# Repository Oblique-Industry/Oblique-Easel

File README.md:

# Oblique Easel
 Code, Electronics, and Industrial Design for the Oblique Easel Artmaschine Cyberdeck

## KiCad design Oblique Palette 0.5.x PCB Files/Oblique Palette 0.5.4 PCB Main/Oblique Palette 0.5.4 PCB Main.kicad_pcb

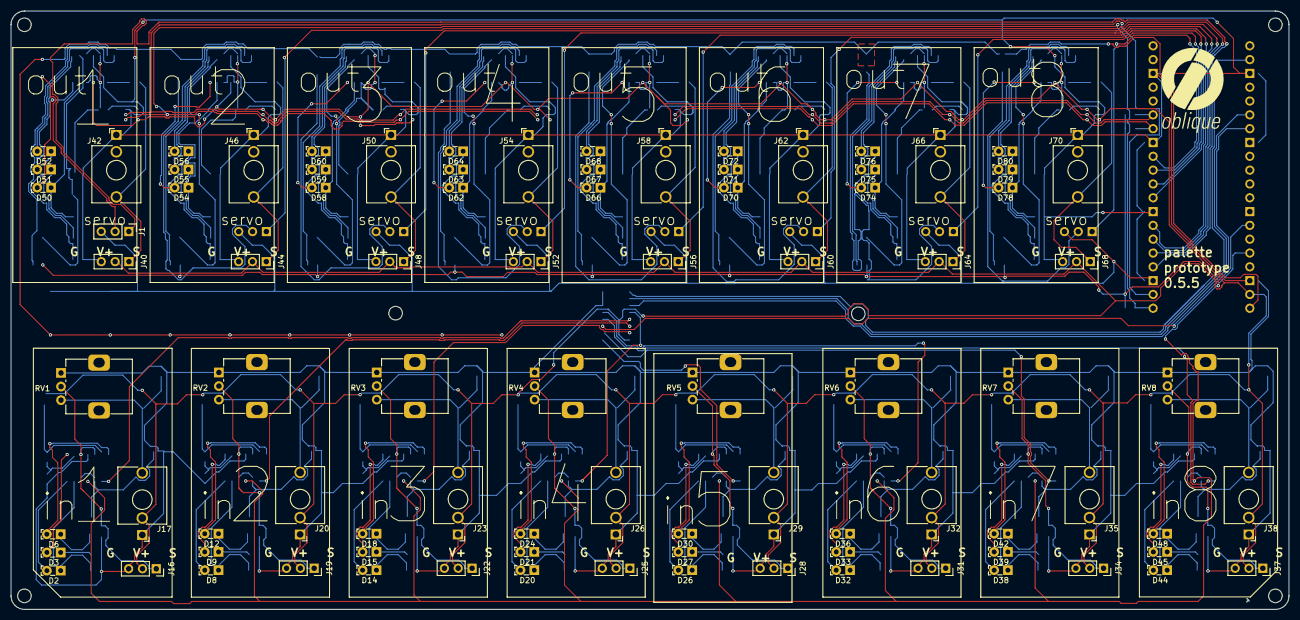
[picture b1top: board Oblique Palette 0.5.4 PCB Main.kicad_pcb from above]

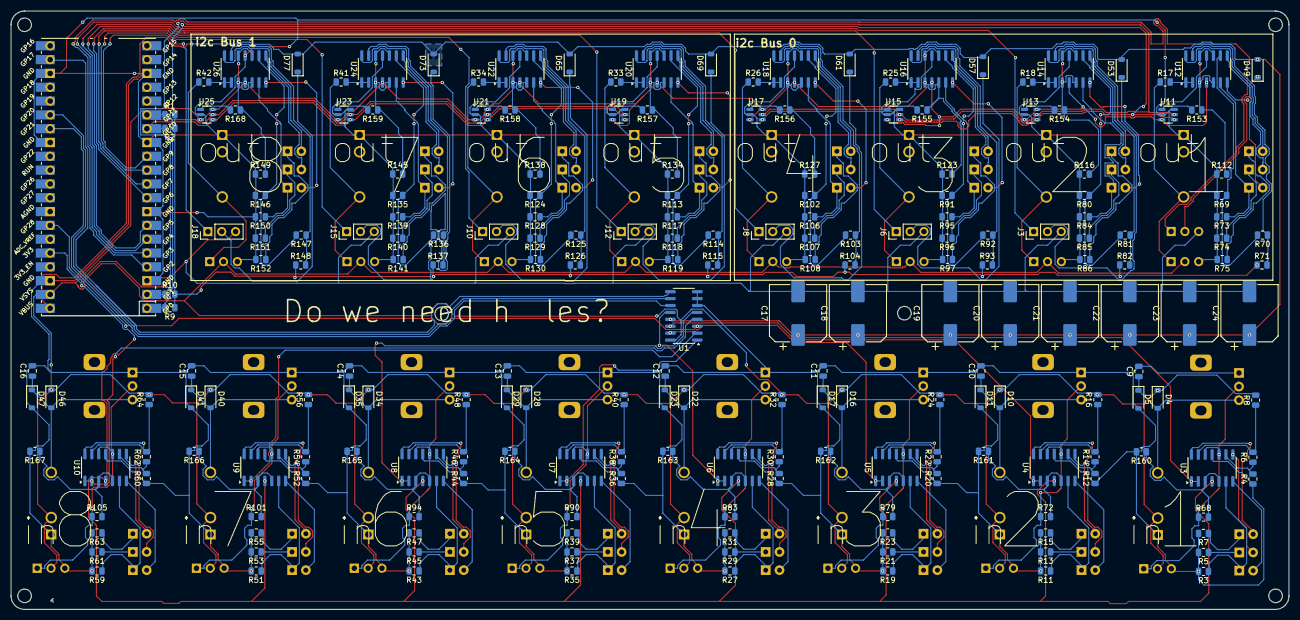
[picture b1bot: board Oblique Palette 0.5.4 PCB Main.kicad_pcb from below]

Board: 2 copper layers, 235.0 x 110.0 mm, 304 parts (213 on the bottom side), 220 nets.

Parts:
C9, C10, C11, C12, C13, C14, C15, C16: 1n; C_0805_2012Metric
C17, C18, C19, C20, C21, C22, C23, C24: 1mF; CP_Elec_10x10
D2, D8, D14, D20, D26, D32, D38, D44, D50, D54, D58, D62, D66, D70, D74, D78: White; LED_SideEmitter_Rectangular_W4.5mm_H1.6mm
D3, D9, D15, D21, D27, D33, D39, D45, D51, D55, D59, D63, D67, D71, D75, D79: Yellow; LED_SideEmitter_Rectangular_W4.5mm_H1.6mm
D4, D5, D10, D11, D16, D17, D22, D23, D28, D29, D34, D35, D40, D41, D46, D47: 1N4148; D_SOD-123
D6, D12, D18, D24, D30, D36, D42, D48, D52, D56, D60, D64, D68, D72, D76, D80: Red; LED_SideEmitter_Rectangular_W4.5mm_H1.6mm
D49, D53, D57, D61, D65, D69, D73, D77: D_SOD-123
G1: LOGO; PCB silkscreen logo
G2: LOGO; PCB silkscreen logotype
J1, J3, J6, J8, J10, J12, J15, J18: Conn_01x03_Male_Pin; PinHeader_1x03_P2.54mm_Vertical
J16, J19, J22, J25, J28, J31, J34, J37, J40, J44, J48, J52, J56, J60, J64, J68: Conn_01x03_Female_Pin; PinSocket_1x03_P2.54mm_Vertical
J17, J20, J23, J26, J29, J32, J35, J38, J42, J46, J50, J54, J58, J62, J66, J70: AudioJack2_SwitchT; Jack_3.5mm_QingPu_WQP-PJ398SM_Vertical_CircularHoles
R1, R2, R9, R10: R33k; R_0805_2012Metric
R3, R11, R19, R27, R35, R43, R51, R59, R73, R84, R95, R106, R117, R128, R139, R150: 1K; R_0805_2012Metric
R4, R12, R20, R28, R36, R44, R52, R60, R69, R80, R91, R102, R113, R124, R135, R146: 300k; R_0805_2012Metric
R5, R7, R13, R15, R21, R23, R29, R31, R37, R39, R45, R47, R53, R55, R61, R63, R74, R75, R85, R86, R96, R97, R107, R108, R118, R119, R129, R130, R140, R141, R151, R152: 127R; R_0805_2012Metric
R6, R14, R22, R30, R38, R46, R54, R62: 110K; R_0805_2012Metric
R8, R16, R24, R32, R40, R48, R56, R64: 150K; R_0805_2012Metric
R17, R18, R25, R26, R33, R34, R41, R42: 100R; R_0805_2012Metric
R68, R72, R79, R83, R90, R94, R101, R105: 100K; R_0805_2012Metric
R70, R81, R92, R103, R114, R125, R136, R147: 110k; R_0805_2012Metric
R71, R82, R93, R104, R115, R126, R137, R148: 150k; R_0805_2012Metric
R112, R116, R123, R127, R134, R138, R145, R149: 200k; R_0805_2012Metric
R153, R154, R155, R156, R157, R158, R159, R168: 100k; R_0805_2012Metric
R160, R161, R162, R163, R164, R165, R166, R167: 200K; R_0805_2012Metric
RV1, RV2, RV3, RV4, RV5, RV6, RV7, RV8: R_Potentiometer_MountingPin; Potentiometer_Alps_RK09K_Single_Vertical
U1: CD4051B; SOIC-16_3.9x9.9mm_P1.27mm
U2: Pico; RPi_Pico_SMD_TH
U3, U4, U5, U6, U7, U8, U9, U10, U12, U14, U16, U18, U20, U22, U24, U26: MCP6004; SOIC-14_3.9x8.7mm_P1.27mm
U11, U13, U15, U17, U19, U21, U23, U25: MCP4725xxx-xCH; SOT-23-6

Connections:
+3.3V: R1.2, R2.1, R9.1, R10.2, R71.1, R82.1, R93.1, R104.1, R115.1, R126.1, R137.1, R148.1, U2.36 (3V3), U3.4 (V+), U4.4 (V+), U5.4 (V+), U6.4 (V+), U7.4 (V+), U8.4 (V+), U9.4 (V+), U10.4 (V+)
/Input 1/ANALOG_CHANNEL: U1.13 (X0), U3.1, U3.2 (-)
/Input 2/ANALOG_CHANNEL: U1.14 (X1), U4.1, U4.2 (-)
/Input 3/ANALOG_CHANNEL: U1.15 (X2), U5.1, U5.2 (-)
/Input 4/ANALOG_CHANNEL: U1.12 (X3), U6.1, U6.2 (-)
/Input 5/ANALOG_CHANNEL: U1.1 (X4), U7.1, U7.2 (-)
/Input 6/ANALOG_CHANNEL: U1.5 (X5), U8.1, U8.2 (-)
/Input 7/ANALOG_CHANNEL: U1.2 (X6), U9.1, U9.2 (-)
/Input 8/ANALOG_CHANNEL: U1.4 (X7), U10.1, U10.2 (-)
GNDREF: C9.2, C10.2, C11.2, C12.2, C13.2, C14.2, C15.2, C16.2, C17.2, C18.2, C19.2, C20.2, C21.2, C22.2, C23.2, C24.2, D5.2 (A), D11.2 (A), D17.2 (A), D23.2 (A), D29.2 (A), D35.2 (A), D41.2 (A), D47.2 (A), J1.3, J3.3, J6.3, J8.3, J10.3, J12.3, J15.3, J16.3, J17.S, J18.3, J19.3, J20.S, J22.3, J23.S, J25.3, J26.S, J28.3, J29.S, J31.3, J32.S, J34.3, J35.S, J37.3, J38.S, J40.3, J42.S, J44.3, J46.S, J48.3, J50.S, J52.3, J54.S, J56.3, J58.S, J60.3, J62.S, J64.3, J66.S, J68.3, J70.S, R3.2, R4.1, R5.2, R7.2, R11.2, R12.1, R13.2, R15.2, R19.2, R20.1, R21.2, R23.2, R27.2, R28.1, R29.2, R31.2, R35.2, R36.1, R37.2, R39.2, R43.2, R44.1, R45.2, R47.2, R51.2, R52.1, R53.2, R55.2, R59.2, R60.1, R61.2, R63.2, R69.2, R73.2, R74.2, R75.2, R80.2, R84.2, R85.2, R86.2, R91.2, R95.2, R96.2, R97.2, R102.2, R106.2, R107.2, R108.2, R112.1, R113.2, R116.1, R117.2, R118.2, R119.2, R123.1, R124.2, R127.1, R128.2, R129.2, R130.2, R134.1, R135.2, R138.1, R139.2, R140.2, R141.2, R145.1, R146.2, R149.1, R150.2, R151.2, R152.2, R160.2, R161.2, R162.2, R163.2, R164.2, R165.2, R166.2, R167.2, RV1.1, RV2.1, RV3.1, RV4.1, RV5.1, RV6.1, RV7.1, RV8.1, U1.6 (INH), U1.7 (VEE), U1.8 (VSS), U2.3 (GND), U2.8 (GND), U2.13 (GND), U2.18 (GND), U2.23 (GND), U2.28 (GND), U2.38 (GND), U3.11 (V-), U4.11 (V-), U5.11 (V-), U6.11 (V-), U7.11 (V-), U8.11 (V-), U9.11 (V-), U10.11 (V-), U11.2 (VSS), U11.6 (A0), U12.11 (V-), U13.2 (VSS), U14.11 (V-), U15.2 (VSS), U15.6 (A0), U16.11 (V-), U17.2 (VSS), U18.11 (V-), U19.2 (VSS), U19.6 (A0), U20.11 (V-), U21.2 (VSS), U22.11 (V-), U23.2 (VSS), U23.6 (A0), U24.11 (V-), U25.2 (VSS), U26.11 (V-)
unnamed: D2.2 (A), U3.7
unnamed: D2.1 (K), R3.1, U3.6 (-)
unnamed: D3.2 (A), U3.8
unnamed: D3.1 (K), R5.1
unnamed: C9.1, D4.2 (A), D5.1 (K), J17.T, RV1.3
unnamed: D6.2 (A), U3.14
unnamed: D6.1 (K), R7.1
unnamed: D8.2 (A), U4.7
unnamed: D8.1 (K), R11.1, U4.6 (-)
unnamed: D9.2 (A), U4.8
unnamed: D9.1 (K), R13.1
unnamed: C10.1, D10.2 (A), D11.1 (K), J20.T, RV2.3
unnamed: D12.2 (A), U4.14
unnamed: D12.1 (K), R15.1
unnamed: D14.2 (A), U5.7
unnamed: D14.1 (K), R19.1, U5.6 (-)
unnamed: D15.2 (A), U5.8
unnamed: D15.1 (K), R21.1
unnamed: C11.1, D16.2 (A), D17.1 (K), J23.T, RV3.3
unnamed: D18.2 (A), U5.14
unnamed: D18.1 (K), R23.1
unnamed: D20.2 (A), U6.7
unnamed: D20.1 (K), R27.1, U6.6 (-)
unnamed: D21.2 (A), U6.8
unnamed: D21.1 (K), R29.1
unnamed: C12.1, D22.2 (A), D23.1 (K), J26.T, RV4.3
unnamed: D24.2 (A), U6.14
unnamed: D24.1 (K), R31.1
unnamed: D26.2 (A), U7.7
unnamed: D26.1 (K), R35.1, U7.6 (-)
unnamed: D27.2 (A), U7.8
unnamed: D27.1 (K), R37.1
unnamed: C13.1, D28.2 (A), D29.1 (K), J29.T, RV5.3
unnamed: D30.2 (A), U7.14
unnamed: D30.1 (K), R39.1
unnamed: D32.2 (A), U8.7
unnamed: D32.1 (K), R43.1, U8.6 (-)
unnamed: D33.2 (A), U8.8
unnamed: D33.1 (K), R45.1
unnamed: C14.1, D34.2 (A), D35.1 (K), J32.T, RV6.3
unnamed: D36.2 (A), U8.14
unnamed: D36.1 (K), R47.1
unnamed: D38.2 (A), U9.7
unnamed: D38.1 (K), R51.1, U9.6 (-)
unnamed: D39.2 (A), U9.8
unnamed: D39.1 (K), R53.1
unnamed: C15.1, D40.2 (A), D41.1 (K), J35.T, RV7.3
unnamed: D42.2 (A), U9.14
unnamed: D42.1 (K), R55.1
unnamed: D44.2 (A), U10.7
unnamed: D44.1 (K), R59.1, U10.6 (-)
unnamed: D45.2 (A), U10.8
unnamed: D45.1 (K), R61.1
unnamed: C16.1, D46.2 (A), D47.1 (K), J38.T, RV8.3
unnamed: D48.2 (A), U10.14
unnamed: D48.1 (K), R63.1
unnamed: D49.1 (K), J1.2
unnamed: D50.2 (A), U12.7
unnamed: D50.1 (K), R73.1, U12.6 (-)
unnamed: D51.2 (A), U12.8
unnamed: D51.1 (K), R74.1
unnamed: D52.2 (A), U12.14
unnamed: D52.1 (K), R75.1
unnamed: D53.1 (K), J3.2
unnamed: D54.2 (A), U14.7
unnamed: D54.1 (K), R84.1, U14.6 (-)
unnamed: D55.2 (A), U14.8
unnamed: D55.1 (K), R85.1
unnamed: D56.2 (A), U14.14
unnamed: D56.1 (K), R86.1
unnamed: D57.1 (K), J6.2
unnamed: D58.2 (A), U16.7
unnamed: D58.1 (K), R95.1, U16.6 (-)
unnamed: D59.2 (A), U16.8
unnamed: D59.1 (K), R96.1
unnamed: D60.2 (A), U16.14
unnamed: D60.1 (K), R97.1
unnamed: D61.1 (K), J8.2
unnamed: D62.2 (A), U18.7
unnamed: D62.1 (K), R106.1, U18.6 (-)
unnamed: D63.2 (A), U18.8
unnamed: D63.1 (K), R107.1
unnamed: D64.2 (A), U18.14
unnamed: D64.1 (K), R108.1
unnamed: D65.1 (K), J10.2
unnamed: D66.2 (A), U20.7
unnamed: D66.1 (K), R117.1, U20.6 (-)
unnamed: D67.2 (A), U20.8
unnamed: D67.1 (K), R118.1
unnamed: D68.2 (A), U20.14
unnamed: D68.1 (K), R119.1
unnamed: D69.1 (K), J12.2
unnamed: D70.2 (A), U22.7
unnamed: D70.1 (K), R128.1, U22.6 (-)
unnamed: D71.2 (A), U22.8
unnamed: D71.1 (K), R129.1
unnamed: D72.2 (A), U22.14
unnamed: D72.1 (K), R130.1
unnamed: D73.1 (K), J15.2
unnamed: D74.2 (A), U24.7
unnamed: D74.1 (K), R139.1, U24.6 (-)
unnamed: D75.2 (A), U24.8
unnamed: D75.1 (K), R140.1
unnamed: D76.2 (A), U24.14
unnamed: D76.1 (K), R141.1
unnamed: D77.1 (K), J18.2
unnamed: D78.2 (A), U26.7
unnamed: D78.1 (K), R150.1, U26.6 (-)
unnamed: D79.2 (A), U26.8
unnamed: D79.1 (K), R151.1
unnamed: D80.2 (A), U26.14
unnamed: D80.1 (K), R152.1
unnamed: J16.1, R68.1, RV1.2, U3.10 (+), U3.12 (+)
unnamed: J19.1, R72.1, RV2.2, U4.10 (+), U4.12 (+)
unnamed: J22.1, R79.1, RV3.2, U5.10 (+), U5.12 (+)
unnamed: J25.1, R83.1, RV4.2, U6.10 (+), U6.12 (+)
unnamed: J28.1, R90.1, RV5.2, U7.10 (+), U7.12 (+)
unnamed: J31.1, R94.1, RV6.2, U8.10 (+), U8.12 (+)
unnamed: J34.1, R101.1, RV7.2, U9.10 (+), U9.12 (+)
unnamed: J37.1, R105.1, RV8.2, U10.10 (+), U10.12 (+)
unnamed: J40.1, J42.T, R17.1
unnamed: J44.1, J46.T, R18.1
unnamed: J48.1, J50.T, R25.1
unnamed: J52.1, J54.T, R26.1
unnamed: J56.1, J58.T, R33.1
unnamed: J60.1, J62.T, R34.1
unnamed: J64.1, J66.T, R41.1
unnamed: J68.1, J70.T, R42.1
unnamed: U1.11 (A), U2.27 (GPIO21)
unnamed: U1.10 (B), U2.26 (GPIO20)
unnamed: U1.9 (C), U2.22 (GPIO17)
unnamed: U1.3 (X), U2.34 (GPIO28_ADC2)
unnamed: R68.2, R160.1, U3.3 (+), U3.5 (+)
unnamed: R4.2, R6.1, U3.9 (-)
unnamed: R6.2, R8.1, U3.13 (-)
unnamed: R72.2, R161.1, U4.3 (+), U4.5 (+)
unnamed: R12.2, R14.1, U4.9 (-)
unnamed: R14.2, R16.1, U4.13 (-)
unnamed: R79.2, R162.1, U5.3 (+), U5.5 (+)
unnamed: R20.2, R22.1, U5.9 (-)
unnamed: R22.2, R24.1, U5.13 (-)
unnamed: R83.2, R163.1, U6.3 (+), U6.5 (+)
unnamed: R28.2, R30.1, U6.9 (-)
unnamed: R30.2, R32.1, U6.13 (-)
unnamed: R90.2, R164.1, U7.3 (+), U7.5 (+)
unnamed: R36.2, R38.1, U7.9 (-)
unnamed: R38.2, R40.1, U7.13 (-)
unnamed: R94.2, R165.1, U8.3 (+), U8.5 (+)
unnamed: R44.2, R46.1, U8.9 (-)
unnamed: R46.2, R48.1, U8.13 (-)
unnamed: R101.2, R166.1, U9.3 (+), U9.5 (+)
unnamed: R52.2, R54.1, U9.9 (-)
unnamed: R54.2, R56.1, U9.13 (-)
unnamed: R105.2, R167.1, U10.3 (+), U10.5 (+)
unnamed: R60.2, R62.1, U10.9 (-)
unnamed: R62.2, R64.1, U10.13 (-)
unnamed: R153.2, U11.1 (VOUT)
unnamed: R112.2, R153.1, U12.3 (+), U12.5 (+), U12.10 (+), U12.12 (+)
unnamed: R17.2, U12.1, U12.2 (-)
unnamed: R69.1, R70.2, U12.9 (-)
unnamed: R70.1, R71.2, U12.13 (-)
unnamed: R154.2, U13.1 (VOUT)
unnamed: R116.2, R154.1, U14.3 (+), U14.5 (+), U14.10 (+), U14.12 (+)
unnamed: R18.2, U14.1, U14.2 (-)
unnamed: R80.1, R81.2, U14.9 (-)
unnamed: R81.1, R82.2, U14.13 (-)
unnamed: R155.2, U15.1 (VOUT)
unnamed: R123.2, R155.1, U16.3 (+), U16.5 (+), U16.10 (+), U16.12 (+)
unnamed: R25.2, U16.1, U16.2 (-)
unnamed: R91.1, R92.2, U16.9 (-)
unnamed: R92.1, R93.2, U16.13 (-)
unnamed: R156.2, U17.1 (VOUT)
unnamed: R127.2, R156.1, U18.3 (+), U18.5 (+), U18.10 (+), U18.12 (+)
unnamed: R26.2, U18.1, U18.2 (-)
unnamed: R102.1, R103.2, U18.9 (-)
unnamed: R103.1, R104.2, U18.13 (-)
unnamed: R157.2, U19.1 (VOUT)
unnamed: R134.2, R157.1, U20.3 (+), U20.5 (+), U20.10 (+), U20.12 (+)
unnamed: R33.2, U20.1, U20.2 (-)
unnamed: R113.1, R114.2, U20.9 (-)
unnamed: R114.1, R115.2, U20.13 (-)
unnamed: R158.2, U21.1 (VOUT)
unnamed: R138.2, R158.1, U22.3 (+), U22.5 (+), U22.10 (+), U22.12 (+)
unnamed: R34.2, U22.1, U22.2 (-)
unnamed: R124.1, R125.2, U22.9 (-)
unnamed: R125.1, R126.2, U22.13 (-)
unnamed: R159.2, U23.1 (VOUT)
unnamed: R145.2, R159.1, U24.3 (+), U24.5 (+), U24.10 (+), U24.12 (+)
unnamed: R41.2, U24.1, U24.2 (-)
unnamed: R135.1, R136.2, U24.9 (-)
unnamed: R136.1, R137.2, U24.13 (-)
unnamed: R168.2, U25.1 (VOUT)
unnamed: R149.2, R168.1, U26.3 (+), U26.5 (+), U26.10 (+), U26.12 (+)
unnamed: R42.2, U26.1, U26.2 (-)
unnamed: R146.1, R147.2, U26.9 (-)
unnamed: R147.1, R148.2, U26.13 (-)
SCL_0: R10.1, U2.2 (GPIO1), U11.5 (SCL), U13.5 (SCL), U15.5 (SCL), U17.5 (SCL)
SCL_1: R1.1, U2.15 (GPIO11), U19.5 (SCL), U21.5 (SCL), U23.5 (SCL), U25.5 (SCL)
SDA_0: R9.2, U2.1 (GPIO0), U11.4 (SDA), U13.4 (SDA), U15.4 (SDA), U17.4 (SDA)
SDA_1: R2.2, U2.14 (GPIO10), U19.4 (SDA), U21.4 (SDA), U23.4 (SDA), U25.4 (SDA)
SERVO_1: J1.1, U2.4 (GPIO2)
SERVO_2: J3.1, U2.5 (GPIO3)
SERVO_3: J6.1, U2.6 (GPIO4)
SERVO_4: J8.1, U2.7 (GPIO5)
SERVO_5: J12.1, U2.9 (GPIO6)
SERVO_6: J10.1, U2.10 (GPIO7)
SERVO_7: J15.1, U2.11 (GPIO8)
SERVO_8: J18.1, U2.12 (GPIO9)
VCC: D4.1 (K), D10.1 (K), D16.1 (K), D22.1 (K), D28.1 (K), D34.1 (K), D40.1 (K), D46.1 (K), J16.2, J17.TN, J19.2, J20.TN, J22.2, J23.TN, J25.2, J26.TN, J28.2, J29.TN, J31.2, J32.TN, J34.2, J35.TN, J37.2, J38.TN, J40.2, J44.2, J48.2, J52.2, J56.2, J60.2, J64.2, J68.2, R8.2, R16.2, R24.2, R32.2, R40.2, R48.2, R56.2, R64.2, U1.16 (VDD), U2.39 (VSYS), U11.3 (VDD), U12.4 (V+), U13.3 (VDD), U13.6 (A0), U14.4 (V+), U15.3 (VDD), U16.4 (V+), U17.3 (VDD), U17.6 (A0), U18.4 (V+), U19.3 (VDD), U20.4 (V+), U21.3 (VDD), U21.6 (A0), U22.4 (V+), U23.3 (VDD), U24.4 (V+), U25.3 (VDD), U25.6 (A0), U26.4 (V+)
Vser: C17.1, C18.1, C19.1, C20.1, C21.1, C22.1, C23.1, C24.1, D49.2 (A), D53.2 (A), D57.2 (A), D61.2 (A), D65.2 (A), D69.2 (A), D73.2 (A), D77.2 (A), U2.40 (VBUS)

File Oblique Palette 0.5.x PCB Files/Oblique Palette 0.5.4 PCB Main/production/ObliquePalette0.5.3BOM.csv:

"Id";"Designator";"Footprint";"Quantity";"Designation";"Supplier and ref";
1;"U12,U4,U3,U18,U14,U16,U22,U8,U26,U24,U10,U6,U9,U7,U5,U20";"SOIC-14_3.9x8.7mm_P1.27mm";16;"MCP6004T-E/SL ";;;
2;"U2";"RPi_Pico_SMD_TH";1;"Pico";;;
3;"D14,D50,D74,D78,D20,D62,D32,D26,D58,D44,D70,D8,D38,D66,D2,D54";"LED_SideEmitter_Rectangular_W4.5mm_H1.6mm";16;"White";;;
4;"C11,C14,C15,C16,C10,C9,C13,C12";"C_0805_2012Metric";8;"1n";;;
5;"R126,R104,R137,R82,R71,R115,R93,R148";"R_0805_2012Metric";8;"150k";;;
6;"J39,J59,J72,J67,J51,J63,J47,J43,J55";"PinHeader_1x02_P2.54mm_Vertical";9;"Conn_01x02_Pin";;;
7;"R113,R80,R20,R52,R124,R91,R28,R44,R69,R36,R146,R60,R102,R135,R4,R12";"R_0805_2012Metric";16;"300k";;;
8;"R123,R149,R145,R127,R134,R116,R112,R138";"R_0805_2012Metric";8;"200k";;;
9;"C7,C2,C3,C4,C6,C1,C5,C8";"CP_Radial_D5.0mm_P2.50mm";8;"100uF";;;
10;"J7,J13,J30,J18,J15,J36,J27,J4,J24,J71,J2,J9,J14,J21,J5,J11,J33";"PinHeader_1x03_P2.54mm_Vertical";17;"Conn_01x03_Male_Pin";;;
11;"R98,R87,R111,R100,R109,R78,R76,R67,R133,R144,R89,R65,R142,R120,R122,R131";"R_0805_2012Metric";16;"10K";;;
12;"R128,R43,R11,R19,R73,R68,R72,R139,R94,R95,R90,R59,R150,R106,R3,R35,R83,R105,R51,R101,R117,R79,R27,R84";"R_0805_2012Metric";24;"1K";;;
13;"R130,R97,R96,R140,R151,R118,R75,R108,R86,R119,R85,R107,R152,R74,R141,R129";"R_0805_2012Metric";16;"127R";;;
14;"R103,R92,R136,R70,R114,R81,R125,R147";"R_0805_2012Metric";8;"110k";;;
15;"J62,J32,J35,J54,J58,J20,J26,J46,J17,J23,J29,J42,J38,J70,J66,J50";"Jack_3.5mm_QingPu_WQP-PJ398SM_Vertical_CircularHoles";16;"AudioJack2_SwitchT";;;
16;"R132,R66,R88,R121,R77,R110,R143,R99";"R_0805_2012Metric";8;"100K";;;
17;"R54,R38,R62,R22,R14,R6,R30,R46";"R_0805_2012Metric";8;"110K";;;
18;"D52,D80,D42,D48,D64,D18,D12,D72,D68,D24,D60,D30,D36,D76,D56,D6";"LED_SideEmitter_Rectangular_W4.5mm_H1.6mm";16;"Red";;;
19;"D51,D79,D59,D63,D75,D67,D3,D45,D21,D39,D71,D55,D27,D9,D15,D33";"LED_SideEmitter_Rectangular_W4.5mm_H1.6mm";16;"Yellow";;;
20;"J68,J44,J52,J40,J56,J48,J64,J60";"PinSocket_1x03_P2.54mm_Vertical";8;"Conn_01x03_Female_Pin";;;
21;"D29,D11,D47,D28,D5,D17,D22,D16,D23,D35,D10,D34,D40,D46,D4,D41";"D_SOD-123";16;"1N4148";;;
22;"R157,R155,R156,R159,R158,R153,R154,R168";"R_0805_2012Metric";8;"100k";;;
23;"U17,U21,U25,U13";"SOT-23-6";4;"MCP4725A1T-E/CH ";;;
24;"R24,R32,R8,R64,R48,R56,R16,R40";"R_0805_2012Metric";8;"150K";;;
25;"RV7,RV2,RV4,RV5,RV8,RV3,RV1,RV6";"Potentiometer_Alps_RK09K_Single_Vertical";8;"R_Potentiometer_MountingPin";;;
26;"R53,R39,R63,R15,R29,R31,R37,R23,R55,R13,R47,R7,R5,R61,R21,R45";"R_0805_2012Metric";16;"128R";;;
27;"U15,U19,U23";"SOT-23-6";3;"MCP4725A0T-E/CH ";;;
28;"U11";"SOT-23-6";1;"MCP4725A0T-E/CH";;;
29;"U1";"SOIC-16_3.9x9.9mm_P1.27mm";1;"CD4051BM96 ";;;

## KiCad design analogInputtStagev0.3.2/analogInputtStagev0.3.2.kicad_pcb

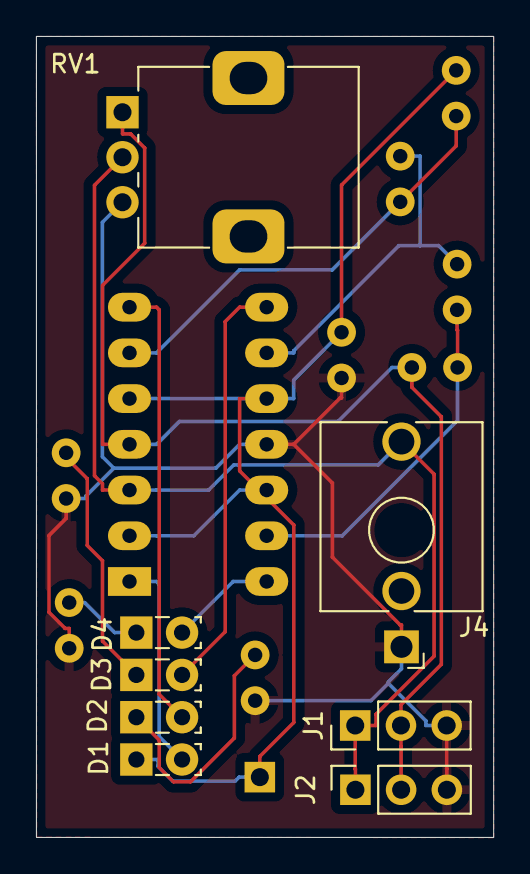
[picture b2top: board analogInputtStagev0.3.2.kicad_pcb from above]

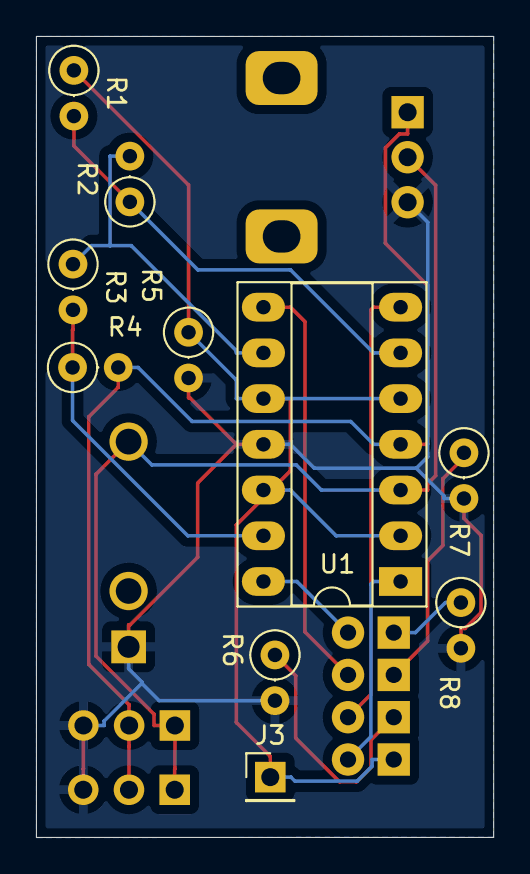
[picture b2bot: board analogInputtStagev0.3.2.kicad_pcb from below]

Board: 2 copper layers, 25.4 x 44.5 mm, 18 parts (10 on the bottom side), 14 nets.

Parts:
D1: White; LED_SideEmitter_Rectangular_W4.5mm_H1.6mm
D2: Blue; LED_SideEmitter_Rectangular_W4.5mm_H1.6mm
D3: Yellow; LED_SideEmitter_Rectangular_W4.5mm_H1.6mm
D4: Red; LED_SideEmitter_Rectangular_W4.5mm_H1.6mm
J1: Conn_01x03_Male_Pin; PinHeader_1x03_P2.54mm_Vertical
J2: Conn_01x03_Female_Pin; PinSocket_1x03_P2.54mm_Vertical
J3: Conn_01x01_Pin; PinHeader_1x01_P2.54mm_Vertical
J4: AudioJack2_SwitchT; Jack_3.5mm_QingPu_WQP-PJ398SM_Vertical_CircularHoles
R1: 5k; R_Axial_DIN0207_L6.3mm_D2.5mm_P2.54mm_Vertical
R2: 2k; R_Axial_DIN0207_L6.3mm_D2.5mm_P2.54mm_Vertical
R3: 2.5k; R_Axial_DIN0207_L6.3mm_D2.5mm_P2.54mm_Vertical
R4: 500R; R_Axial_DIN0207_L6.3mm_D2.5mm_P2.54mm_Vertical
R5, R6, R7, R8: 1k; R_Axial_DIN0207_L6.3mm_D2.5mm_P2.54mm_Vertical
RV1: R_Potentiometer_MountingPin; Potentiometer_Alps_RK09K_Single_Vertical
U1: MCP6004; DIP-14_W7.62mm_Socket_LongPads

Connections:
GNDREF: J1.3, J2.3, J4.S, R5.2, R6.2, R7.2, R8.2, RV1.3, U1.11 (V-)
unnamed: D1.2 (A), U1.1
unnamed: D1.1 (K), J3.1, R1.1, R5.1, U1.2 (-), U1.5 (+), U1.10 (+), U1.12 (+)
unnamed: D2.2 (A), U1.7
unnamed: D2.1 (K), R6.1
unnamed: D3.2 (A), U1.8
unnamed: D3.1 (K), R7.1
unnamed: D4.2 (A), U1.14
unnamed: D4.1 (K), R8.1
unnamed: J1.1, J2.1, J4.T, RV1.2, U1.3 (+)
unnamed: R1.2, R2.1, U1.6 (-)
unnamed: R2.2, R3.1, U1.9 (-)
unnamed: R3.2, R4.1, U1.13 (-)
VCC: J1.2, J2.2, R4.2, RV1.1, U1.4 (V+)

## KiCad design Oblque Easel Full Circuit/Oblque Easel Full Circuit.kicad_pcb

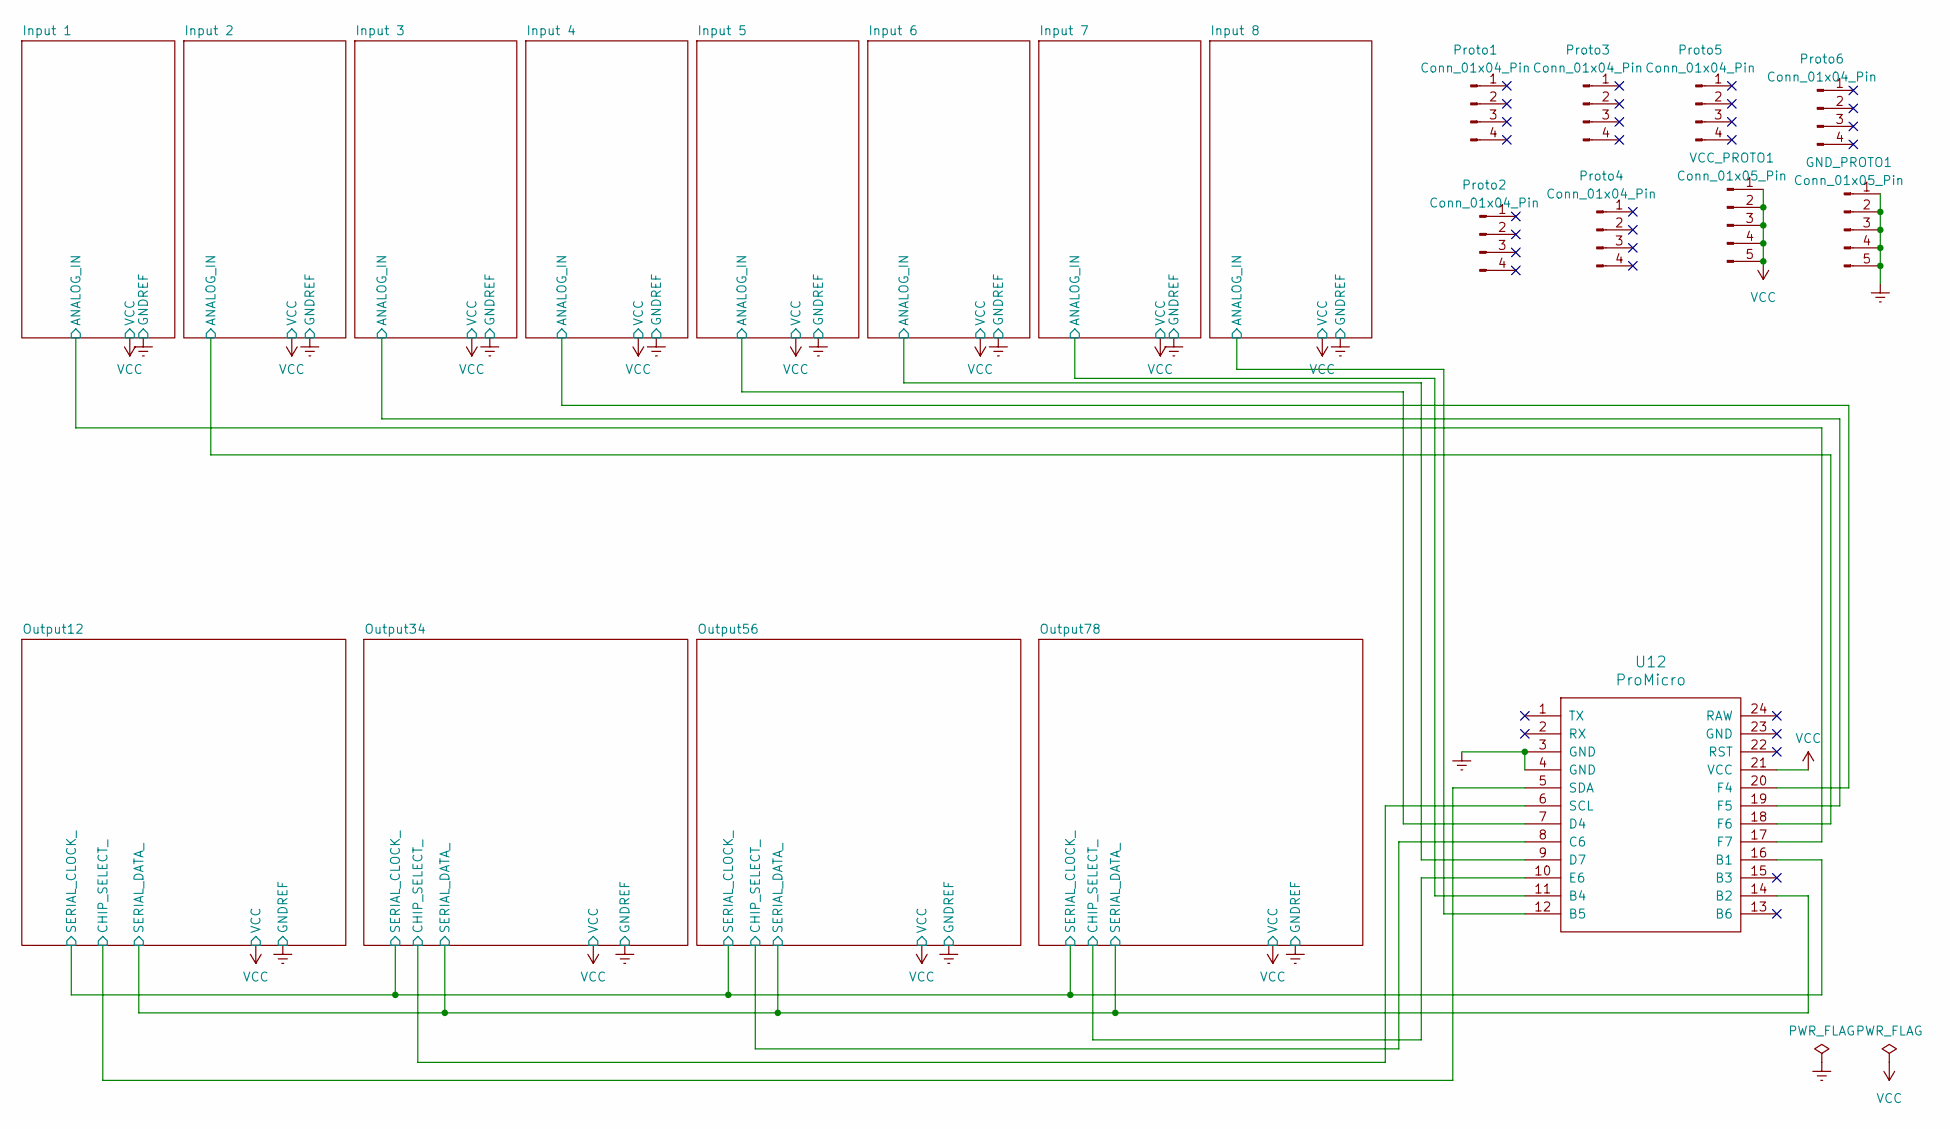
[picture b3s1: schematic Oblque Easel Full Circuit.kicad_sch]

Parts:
GND_PROTO1: Conn_01x05_Pin; PinHeader_1x05_P2.54mm_Vertical
Proto1, Proto2, Proto3, Proto4, Proto5, Proto6: Conn_01x04_Pin; PinHeader_1x04_P2.54mm_Vertical
U12: ProMicro; ProMicro-EnforcedTop
VCC_PROTO1: Conn_01x05_Pin; PinHeader_1x05_P2.54mm_Vertical

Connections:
/Input 1/ANALOG_IN: U12.17 (F7); also elsewhere on the board
/Input 2/ANALOG_IN: U12.18 (F6); also elsewhere on the board
/Input 3/ANALOG_IN: U12.19 (F5); also elsewhere on the board
/Input 4/ANALOG_IN: U12.20 (F4); also elsewhere on the board
/Input 5/ANALOG_IN: U12.7 (D4); also elsewhere on the board
/Input 6/ANALOG_IN: U12.9 (D7); also elsewhere on the board
/Input 7/ANALOG_IN: U12.11 (B4); also elsewhere on the board
/Input 8/ANALOG_IN: U12.12 (B5); also elsewhere on the board
/Output12/CHIP_SELECT_: U12.5 (SDA); also elsewhere on the board
/Output12/SERIAL_CLOCK_: U12.16 (B1); also elsewhere on the board
/Output12/SERIAL_DATA_: U12.14 (B2); also elsewhere on the board
/Output34/CHIP_SELECT_: U12.6 (SCL); also elsewhere on the board
/Output56/CHIP_SELECT_: U12.8 (C6); also elsewhere on the board
/Output78/CHIP_SELECT_: U12.10 (E6); also elsewhere on the board
GNDREF: GND_PROTO1.1, GND_PROTO1.2, GND_PROTO1.3, GND_PROTO1.4, GND_PROTO1.5, U12.3 (GND), U12.4 (GND); also elsewhere on the board
VCC: U12.21 (VCC), VCC_PROTO1.1, VCC_PROTO1.2, VCC_PROTO1.3, VCC_PROTO1.4, VCC_PROTO1.5; also elsewhere on the board

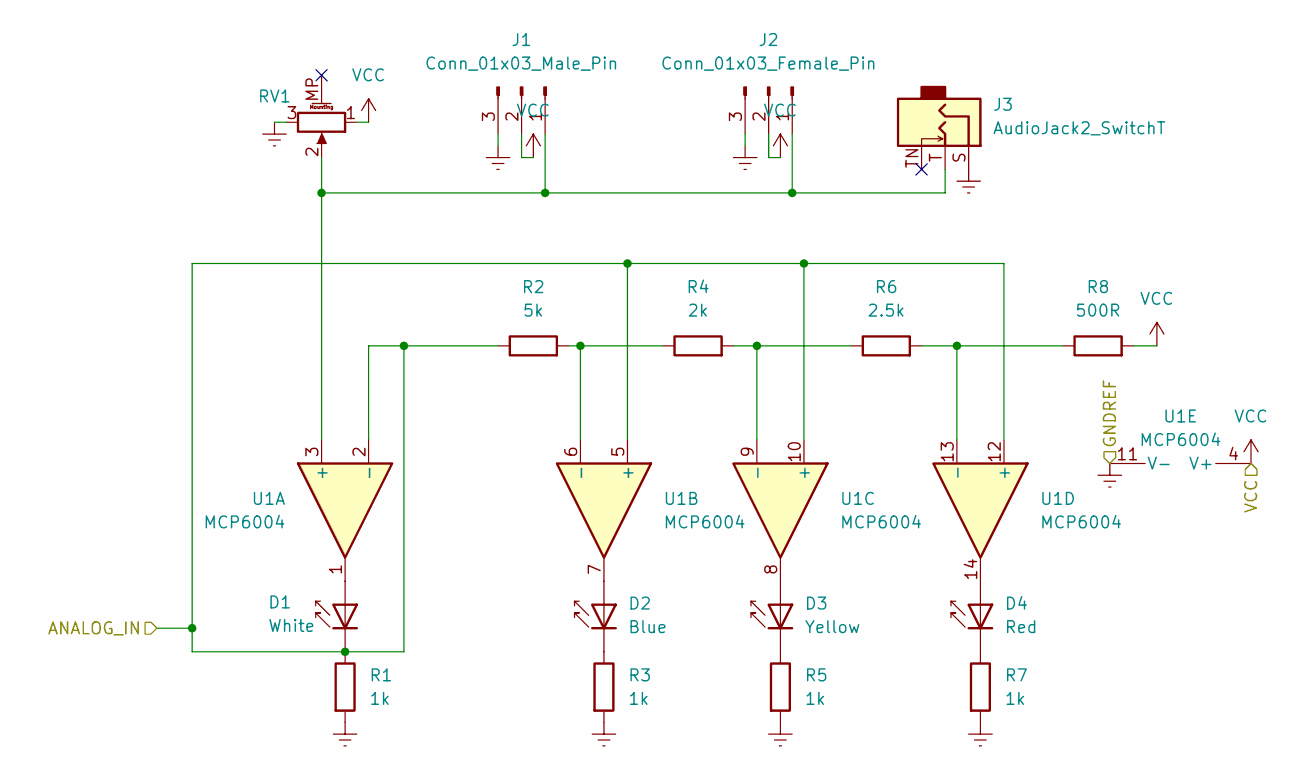
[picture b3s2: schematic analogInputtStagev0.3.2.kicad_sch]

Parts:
D1: White; LED_SideEmitter_Rectangular_W4.5mm_H1.6mm
D2: Blue; LED_SideEmitter_Rectangular_W4.5mm_H1.6mm
D3: Yellow; LED_SideEmitter_Rectangular_W4.5mm_H1.6mm
D4: Red; LED_SideEmitter_Rectangular_W4.5mm_H1.6mm
J1: Conn_01x03_Male_Pin; PinHeader_1x03_P2.54mm_Vertical
J2: Conn_01x03_Female_Pin; PinSocket_1x03_P2.54mm_Vertical
J3: AudioJack2_SwitchT; Jack_3.5mm_QingPu_WQP-PJ398SM_Vertical_CircularHoles
R1, R3, R5, R7: 1k; R_Axial_DIN0207_L6.3mm_D2.5mm_P2.54mm_Vertical
R2: 5k; R_Axial_DIN0207_L6.3mm_D2.5mm_P2.54mm_Vertical
R4: 2k; R_Axial_DIN0207_L6.3mm_D2.5mm_P2.54mm_Vertical
R6: 2.5k; R_Axial_DIN0207_L6.3mm_D2.5mm_P2.54mm_Vertical
R8: 500R; R_Axial_DIN0207_L6.3mm_D2.5mm_P2.54mm_Vertical
RV1: R_Potentiometer_MountingPin; Potentiometer_Alps_RK09K_Single_Vertical
U1: MCP6004; DIP-14_W7.62mm_Socket_LongPads

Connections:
/Input 1/ANALOG_IN: D1.1 (K), R1.1, R2.1, U1.2 (-), U1.5 (+), U1.10 (+), U1.12 (+); also elsewhere on the board
GNDREF: J1.3, J2.3, J3.S, R1.2, R3.2, R5.2, R7.2, RV1.3, U1.11 (V-); also elsewhere on the board
unnamed: D1.2 (A), U1.1
unnamed: D2.2 (A), U1.7
unnamed: D2.1 (K), R3.1
unnamed: D3.2 (A), U1.8
unnamed: D3.1 (K), R5.1
unnamed: D4.2 (A), U1.14
unnamed: D4.1 (K), R7.1
unnamed: J1.1, J2.1, J3.T, RV1.2, U1.3 (+)
unnamed: R2.2, R4.1, U1.6 (-)
unnamed: R4.2, R6.1, U1.9 (-)
unnamed: R6.2, R8.1, U1.13 (-)
VCC: J1.2, J2.2, R8.2, RV1.1, U1.4 (V+); also elsewhere on the board

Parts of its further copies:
D5, D9, D13, D17, D21, D25, D29: White; LED_SideEmitter_Rectangular_W4.5mm_H1.6mm
D6, D10, D14, D18, D22, D26, D30: Blue; LED_SideEmitter_Rectangular_W4.5mm_H1.6mm
D7, D11, D15, D19, D23, D27, D31: Yellow; LED_SideEmitter_Rectangular_W4.5mm_H1.6mm
D8, D12, D16, D20, D24, D28, D32: Red; LED_SideEmitter_Rectangular_W4.5mm_H1.6mm
J4, J7, J10, J13, J16, J19, J22: Conn_01x03_Male_Pin; PinHeader_1x03_P2.54mm_Vertical
J5, J8, J11, J14, J17, J20, J23: Conn_01x03_Female_Pin; PinSocket_1x03_P2.54mm_Vertical
J6, J9, J12, J15, J18, J21, J24: AudioJack2_SwitchT; Jack_3.5mm_QingPu_WQP-PJ398SM_Vertical_CircularHoles
R9, R11, R13, R15, R17, R19, R21, R23, R25, R27, R29, R31, R33, R35, R37, R39, R41, R43, R45, R47, R49, R51, R53, R55, R57, R59, R61, R63: 1k; R_Axial_DIN0207_L6.3mm_D2.5mm_P2.54mm_Vertical
R10, R18, R26, R34, R42, R50, R58: 5k; R_Axial_DIN0207_L6.3mm_D2.5mm_P2.54mm_Vertical
R12, R20, R28, R36, R44, R52, R60: 2k; R_Axial_DIN0207_L6.3mm_D2.5mm_P2.54mm_Vertical
R14, R22, R30, R38, R46, R54, R62: 2.5k; R_Axial_DIN0207_L6.3mm_D2.5mm_P2.54mm_Vertical
R16, R24, R32, R40, R48, R56, R64: 500R; R_Axial_DIN0207_L6.3mm_D2.5mm_P2.54mm_Vertical
RV2, RV3, RV4, RV5, RV6, RV7, RV8: R_Potentiometer_MountingPin; Potentiometer_Alps_RK09K_Single_Vertical
U2, U3, U4, U5, U6, U7, U8: MCP6004; DIP-14_W7.62mm_Socket_LongPads

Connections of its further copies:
/Input 2/ANALOG_IN: D5.1 (K), R9.1, R10.1, U2.2 (-), U2.5 (+), U2.10 (+), U2.12 (+); also elsewhere on the board
/Input 3/ANALOG_IN: D9.1 (K), R17.1, R18.1, U3.2 (-), U3.5 (+), U3.10 (+), U3.12 (+); also elsewhere on the board
/Input 4/ANALOG_IN: D13.1 (K), R25.1, R26.1, U4.2 (-), U4.5 (+), U4.10 (+), U4.12 (+); also elsewhere on the board
/Input 5/ANALOG_IN: D17.1 (K), R33.1, R34.1, U5.2 (-), U5.5 (+), U5.10 (+), U5.12 (+); also elsewhere on the board
/Input 6/ANALOG_IN: D21.1 (K), R41.1, R42.1, U6.2 (-), U6.5 (+), U6.10 (+), U6.12 (+); also elsewhere on the board
/Input 7/ANALOG_IN: D25.1 (K), R49.1, R50.1, U7.2 (-), U7.5 (+), U7.10 (+), U7.12 (+); also elsewhere on the board
/Input 8/ANALOG_IN: D29.1 (K), R57.1, R58.1, U8.2 (-), U8.5 (+), U8.10 (+), U8.12 (+); also elsewhere on the board
GNDREF: J4.3, J5.3, J6.S, J7.3, J8.3, J9.S, J10.3, J11.3, J12.S, J13.3, J14.3, J15.S, J16.3, J17.3, J18.S, J19.3, J20.3, J21.S, J22.3, J23.3, J24.S, R9.2, R11.2, R13.2, R15.2, R17.2, R19.2, R21.2, R23.2, R25.2, R27.2, R29.2, R31.2, R33.2, R35.2, R37.2, R39.2, R41.2, R43.2, R45.2, R47.2, R49.2, R51.2, R53.2, R55.2, R57.2, R59.2, R61.2, R63.2, RV2.3, RV3.3, RV4.3, RV5.3, RV6.3, RV7.3, RV8.3, U2.11 (V-), U3.11 (V-), U4.11 (V-), U5.11 (V-), U6.11 (V-), U7.11 (V-), U8.11 (V-); also elsewhere on the board
unnamed: D5.2 (A), U2.1
unnamed: D6.2 (A), U2.7
unnamed: D6.1 (K), R11.1
unnamed: D7.2 (A), U2.8
unnamed: D7.1 (K), R13.1
unnamed: D8.2 (A), U2.14
unnamed: D8.1 (K), R15.1
unnamed: D9.2 (A), U3.1
unnamed: D10.2 (A), U3.7
unnamed: D10.1 (K), R19.1
unnamed: D11.2 (A), U3.8
unnamed: D11.1 (K), R21.1
unnamed: D12.2 (A), U3.14
unnamed: D12.1 (K), R23.1
unnamed: D13.2 (A), U4.1
unnamed: D14.2 (A), U4.7
unnamed: D14.1 (K), R27.1
unnamed: D15.2 (A), U4.8
unnamed: D15.1 (K), R29.1
unnamed: D16.2 (A), U4.14
unnamed: D16.1 (K), R31.1
unnamed: D17.2 (A), U5.1
unnamed: D18.2 (A), U5.7
unnamed: D18.1 (K), R35.1
unnamed: D19.2 (A), U5.8
unnamed: D19.1 (K), R37.1
unnamed: D20.2 (A), U5.14
unnamed: D20.1 (K), R39.1
unnamed: D21.2 (A), U6.1
unnamed: D22.2 (A), U6.7
unnamed: D22.1 (K), R43.1
unnamed: D23.2 (A), U6.8
unnamed: D23.1 (K), R45.1
unnamed: D24.2 (A), U6.14
unnamed: D24.1 (K), R47.1
unnamed: D25.2 (A), U7.1
unnamed: D26.2 (A), U7.7
unnamed: D26.1 (K), R51.1
unnamed: D27.2 (A), U7.8
unnamed: D27.1 (K), R53.1
unnamed: D28.2 (A), U7.14
unnamed: D28.1 (K), R55.1
unnamed: D29.2 (A), U8.1
unnamed: D30.2 (A), U8.7
unnamed: D30.1 (K), R59.1
unnamed: D31.2 (A), U8.8
unnamed: D31.1 (K), R61.1
unnamed: D32.2 (A), U8.14
unnamed: D32.1 (K), R63.1
unnamed: J4.1, J5.1, J6.T, RV2.2, U2.3 (+)
unnamed: J7.1, J8.1, J9.T, RV3.2, U3.3 (+)
unnamed: J10.1, J11.1, J12.T, RV4.2, U4.3 (+)
unnamed: J13.1, J14.1, J15.T, RV5.2, U5.3 (+)
unnamed: J16.1, J17.1, J18.T, RV6.2, U6.3 (+)
unnamed: J19.1, J20.1, J21.T, RV7.2, U7.3 (+)
unnamed: J22.1, J23.1, J24.T, RV8.2, U8.3 (+)
unnamed: R10.2, R12.1, U2.6 (-)
unnamed: R12.2, R14.1, U2.9 (-)
unnamed: R14.2, R16.1, U2.13 (-)
unnamed: R18.2, R20.1, U3.6 (-)
unnamed: R20.2, R22.1, U3.9 (-)
unnamed: R22.2, R24.1, U3.13 (-)
unnamed: R26.2, R28.1, U4.6 (-)
unnamed: R28.2, R30.1, U4.9 (-)
unnamed: R30.2, R32.1, U4.13 (-)
unnamed: R34.2, R36.1, U5.6 (-)
unnamed: R36.2, R38.1, U5.9 (-)
unnamed: R38.2, R40.1, U5.13 (-)
unnamed: R42.2, R44.1, U6.6 (-)
unnamed: R44.2, R46.1, U6.9 (-)
unnamed: R46.2, R48.1, U6.13 (-)
unnamed: R50.2, R52.1, U7.6 (-)
unnamed: R52.2, R54.1, U7.9 (-)
unnamed: R54.2, R56.1, U7.13 (-)
unnamed: R58.2, R60.1, U8.6 (-)
unnamed: R60.2, R62.1, U8.9 (-)
unnamed: R62.2, R64.1, U8.13 (-)
VCC: J4.2, J5.2, J7.2, J8.2, J10.2, J11.2, J13.2, J14.2, J16.2, J17.2, J19.2, J20.2, J22.2, J23.2, R16.2, R24.2, R32.2, R40.2, R48.2, R56.2, R64.2, RV2.1, RV3.1, RV4.1, RV5.1, RV6.1, RV7.1, RV8.1, U2.4 (V+), U3.4 (V+), U4.4 (V+), U5.4 (V+), U6.4 (V+), U7.4 (V+), U8.4 (V+); also elsewhere on the board
